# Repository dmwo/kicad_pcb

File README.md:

# kicad_pcb
 A collection of personal KiCAD PCBs

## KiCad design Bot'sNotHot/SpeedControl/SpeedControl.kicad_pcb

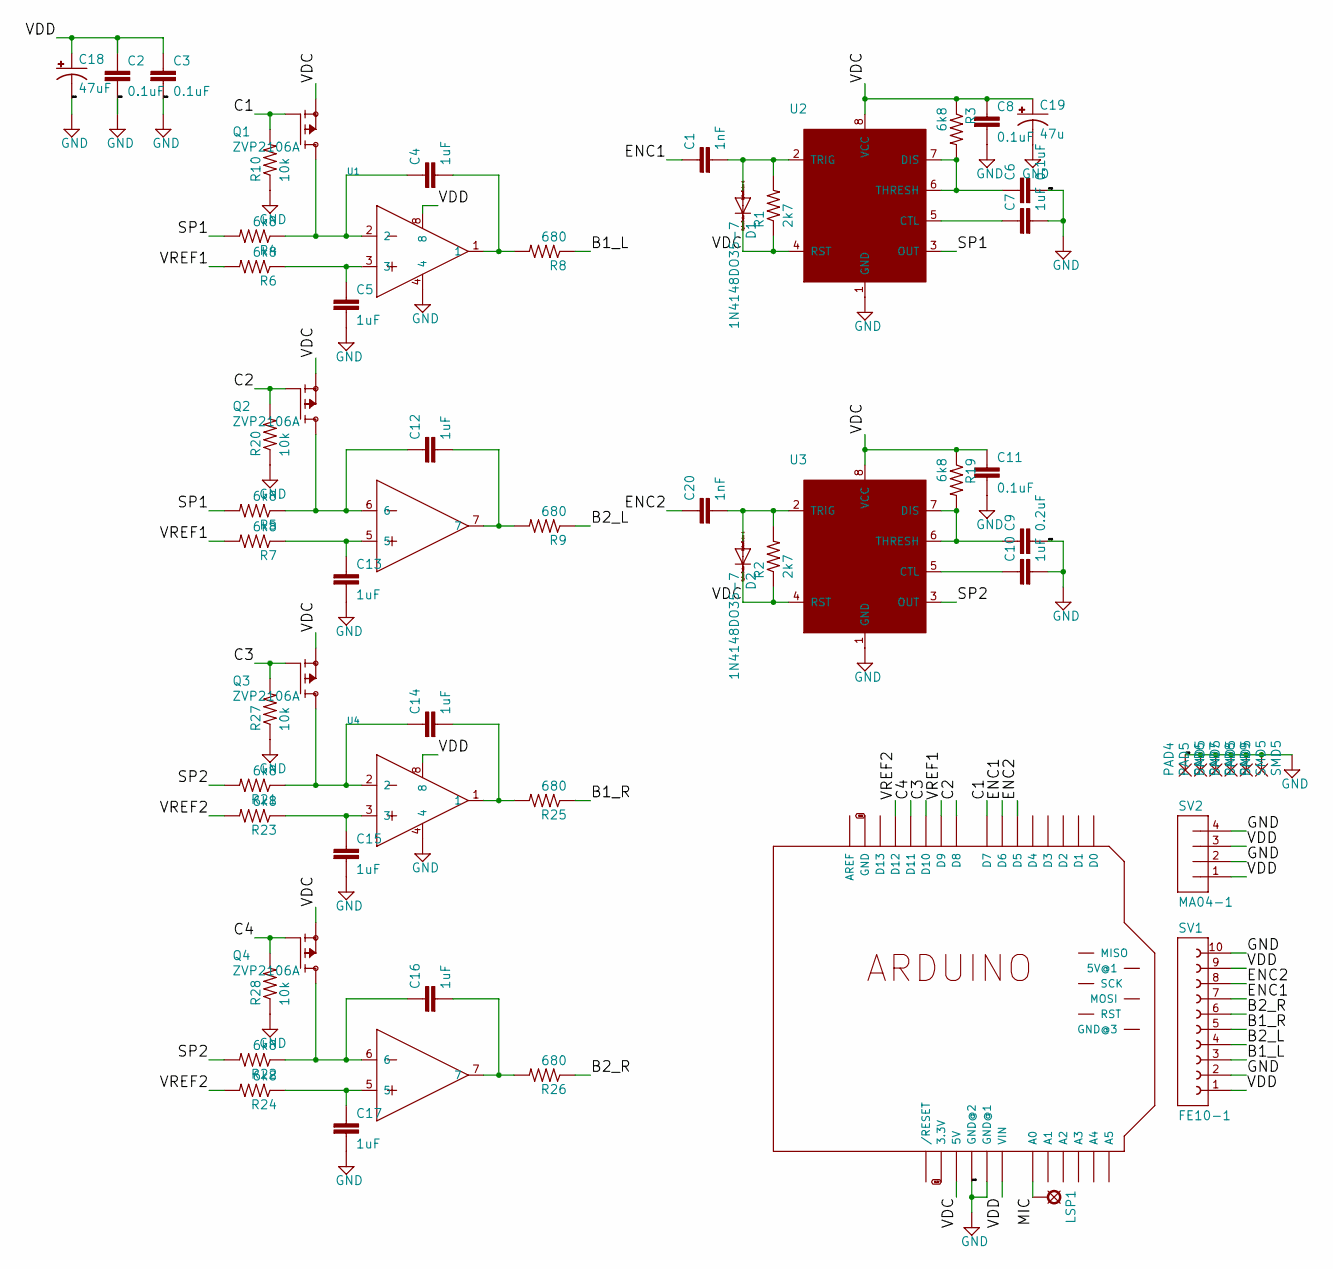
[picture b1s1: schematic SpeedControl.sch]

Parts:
C1, C20: 1nF; C0805
C2, C3, C6, C8, C11: 0.1uF; C0805
C4, C5, C7, C10, C12, C13, C14, C15, C16, C17: 1uF; C0805
C9: 0.2uF; C0805
C18: 47uF; PANASONIC_C
C19: 47u; PANASONIC_C
D1, D2: 1N4148DO35-7; DO35-7
LSP1: SE11
M1: ARDUINO_R3_ICSP_NODIM; ARDUINOR3_ICSP_NODIM
PAD4, PAD5, PAD6, PAD7, PAD8, PAD9: SMD5; SMD2,54-5,08
Q1, Q2, Q3, Q4: ZVP2106A; TO92-BCE
R1, R2: 2k7; R0805
R3, R4, R5, R6, R7, R19, R21, R22, R23, R24: 6k8; R0805
R8, R9, R25, R26: 680; R0805
R10, R20, R27, R28: 10k; R0805
SV1: FE10-1; FE10
SV2: MA04-1
U1, U4: TLV272; DIL08
U2, U3: 555CN; DIL08

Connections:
3.3V: M1.3V (3.3V)
/B1_L: R8.1, SV1.3
/B1_R: R25.1, SV1.5
/B2_L: R9.1, SV1.4
/B2_R: R26.1, SV1.6
/C1: M1.D7, Q1.G, R10.2
/C2: M1.D8, Q2.G, R20.2
/C3: M1.D10, Q3.G, R27.2
/C4: M1.D11, Q4.G, R28.2
/ENC1: C1.1, M1.D6, SV1.7
/ENC2: C20.1, M1.D5, SV1.8
/MIC: LSP1.MP, M1.A0
/SP1: R4.2, R5.2, U2.3 (OUT)
/SP2: R21.2, R22.2, U3.3 (OUT)
/VDC: C8.1, C11.1, C19.+, D1.C, D2.C, M1.5V, Q1.S, Q2.S, Q3.S, Q4.S, R1.1, R2.1, R3.1, R19.1, U2.4 (RST), U2.8 (VCC), U3.4 (RST), U3.8 (VCC)
/VDD: C2.1, C3.1, C18.+, M1.VIN, SV1.1, SV1.9, SV2.1, SV2.3, U1.8, U4.8
/VREF1: M1.D9, R6.2, R7.2
/VREF2: M1.D12, R23.2, R24.2
GND: C2.2, C3.2, C5.2, C6.2, C7.2, C8.2, C9.2, C10.2, C11.2, C13.2, C15.2, C17.2, C18.-, C19.-, M1.GND, M1.GND@1, M1.GND@2, PAD4.1, PAD5.1, PAD6.1, PAD7.1, PAD8.1, PAD9.1, R10.1, R20.1, R27.1, R28.1, SV1.2, SV1.10, SV2.2, SV2.4, U1.4, U2.1 (GND), U3.1 (GND), U4.4
unnamed: C1.2, D1.A, R1.2, U2.2 (TRIG)
unnamed: C4.1, Q1.D, R4.1, U1.2
unnamed: C4.2, R8.2, U1.1
unnamed: C5.1, R6.1, U1.3
unnamed: C6.1, R3.2, U2.6 (THRESH), U2.7 (DIS)
unnamed: C7.1, U2.5 (CTL)
unnamed: C9.1, R19.2, U3.6 (THRESH), U3.7 (DIS)
unnamed: C10.1, U3.5 (CTL)
unnamed: C12.1, Q2.D, R5.1, U1.6
unnamed: C12.2, R9.2, U1.7
unnamed: C13.1, R7.1, U1.5
unnamed: C14.1, Q3.D, R21.1, U4.2
unnamed: C14.2, R25.2, U4.1
unnamed: C15.1, R23.1, U4.3
unnamed: C16.1, Q4.D, R22.1, U4.6
unnamed: C16.2, R26.2, U4.7
unnamed: C17.1, R24.1, U4.5
unnamed: C20.2, D2.A, R2.2, U3.2 (TRIG)

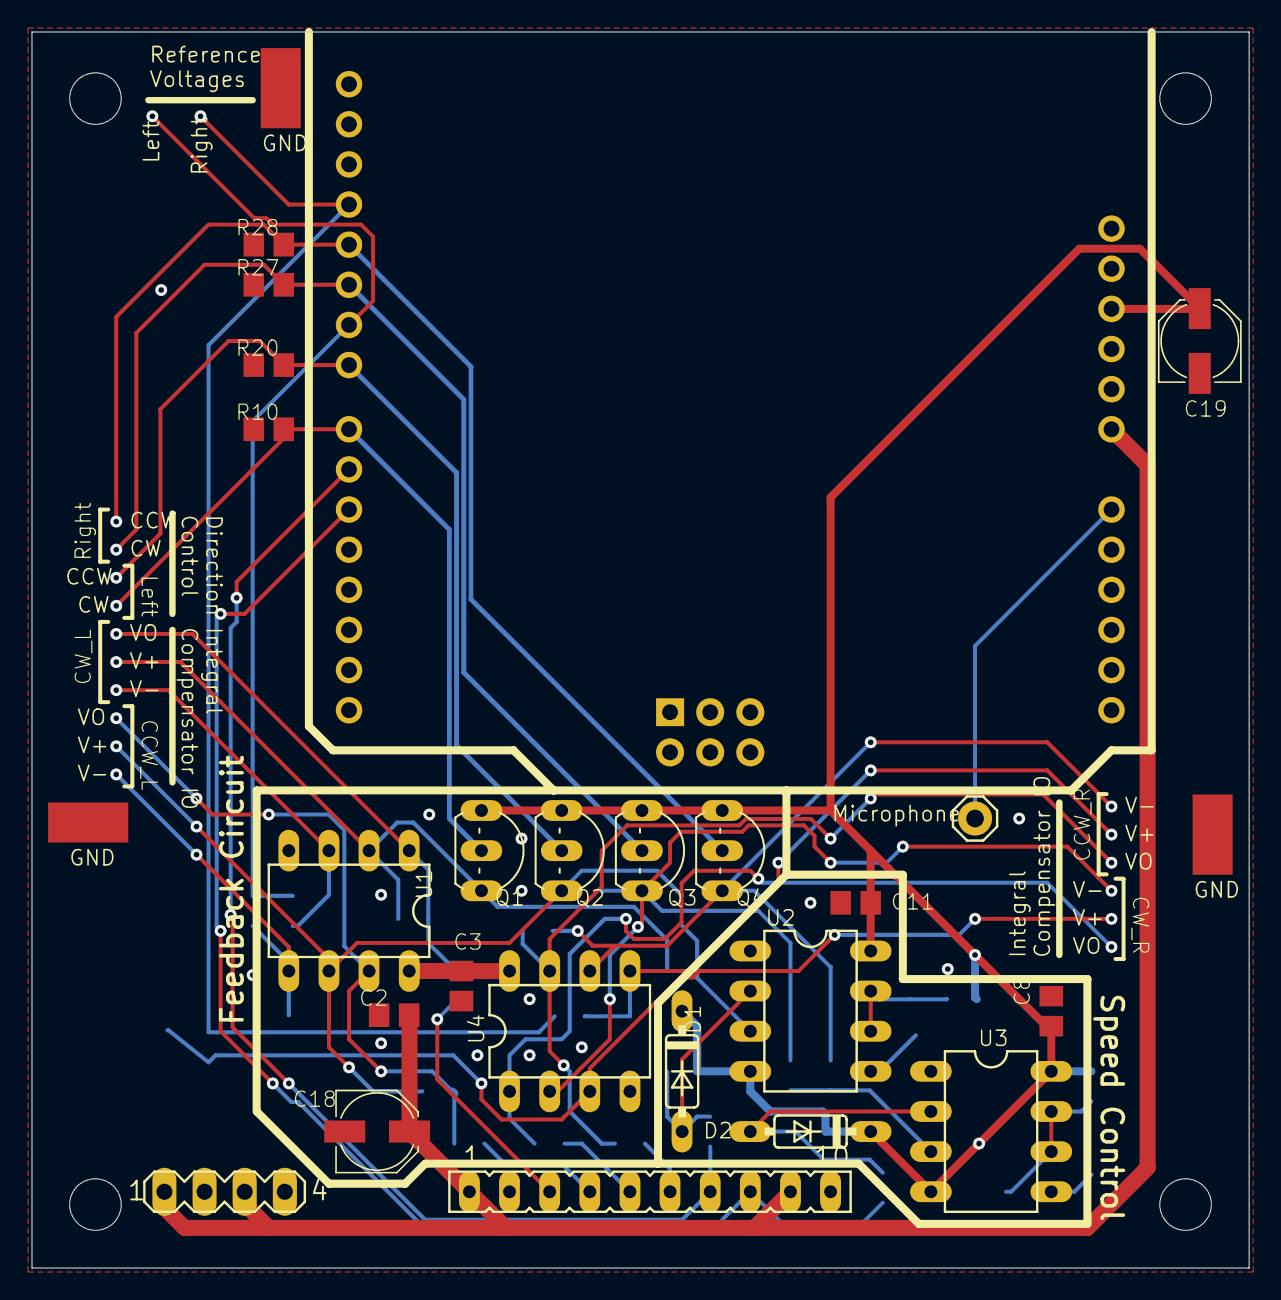
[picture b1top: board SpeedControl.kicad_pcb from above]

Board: 2 copper layers, 77.0 x 78.2 mm, 64 parts (0 on the bottom side), 36 nets.

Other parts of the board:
@HOLE0, @HOLE1, @HOLE2, @HOLE3: (no value)

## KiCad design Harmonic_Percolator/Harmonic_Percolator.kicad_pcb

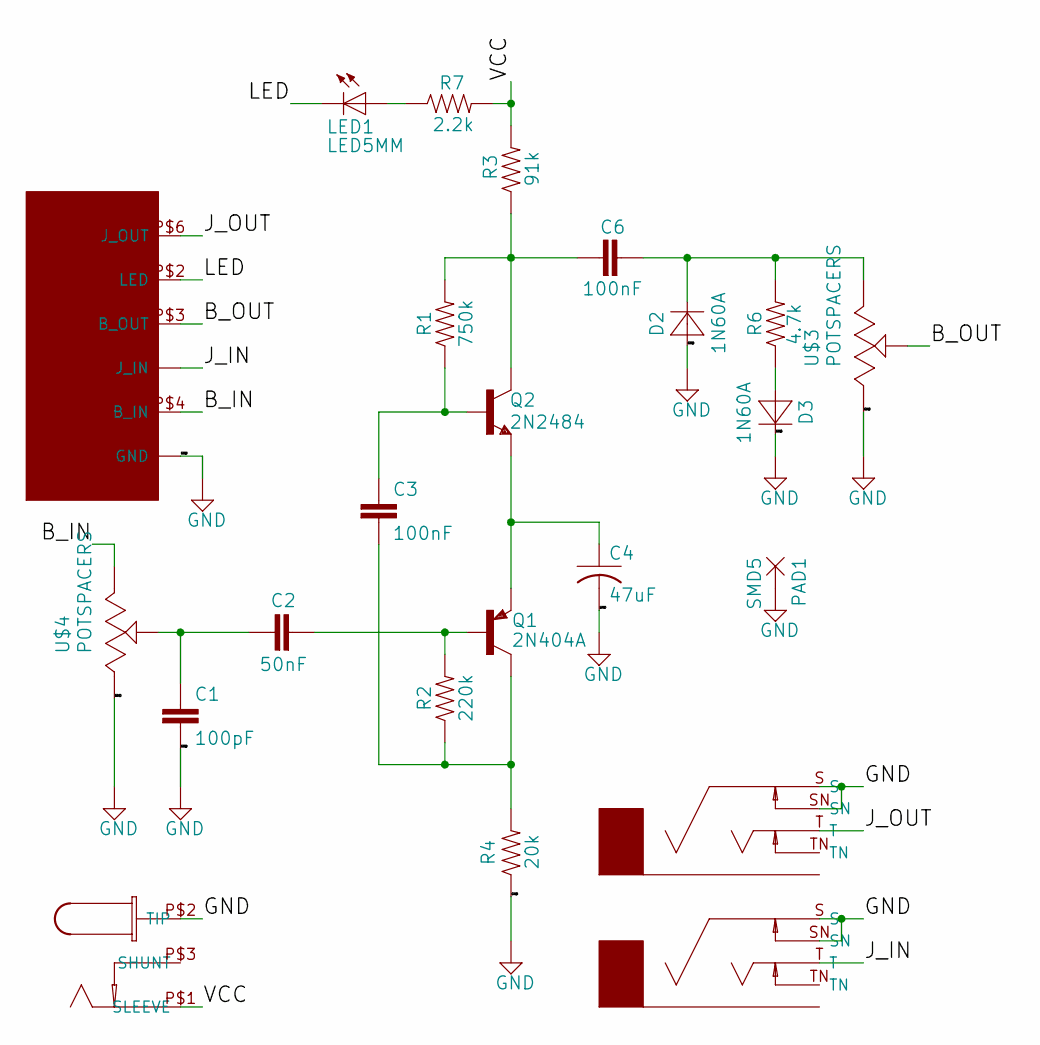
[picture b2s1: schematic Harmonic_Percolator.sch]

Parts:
C1: 100pF; C050-025X075
C2: 50nF; C150-054X183
C3, C6: 100nF; C050-024X044
C4: 47uF; C025-024X044
D2, D3: 1N60A; DO-7
LED1: LED5MM
PAD1: SMD5; SMD2,54-5,08
PS1: DCJACK
Q1: 2N404A; TO5
Q2: 2N2484; TO18
R1: 750k; 0207_7
R2: 220k; 0207_7
R3: 91k; 0207_7
R4: 20k; 0207_7
R6: 4.7k; 0207_7
R7: 2.2k; 0207_7
S1: FOOTSWITCH
U$1, U$2: NEUTRIKENCJACK
U$3, U$4: POTSPACERS

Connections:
/B_IN: S1.P$4 (B_IN), U$4.P$3 (E)
/B_OUT: S1.P$3 (B_OUT), U$3.P$2 (S)
/J_IN: S1.P$1 (J_IN), S1.P$9 (J_IN), U$2.T
/J_OUT: S1.P$6 (J_OUT), U$1.T
/LED: LED1.K (C), S1.P$2 (LED)
/VCC: PS1.P$1 (SLEEVE), R3.2, R7.2
GND: C1.2, C4.2, D2.P$2 (A), D3.P$1 (C), PAD1.1, PS1.P$2 (TIP), R4.1, S1.P$5 (GND), S1.P$7 (GND), U$1.S, U$1.SN, U$2.S, U$2.SN, U$3.P$1 (A), U$4.P$1 (A)
unnamed: C1.1, C2.1, U$4.P$2 (S)
unnamed: C2.2, Q1.2 (B), R2.2
unnamed: C3.1, Q2.2 (B), R1.1
unnamed: C3.2, Q1.3 (C), R2.1, R4.2
unnamed: C4.1, Q1.1 (E), Q2.1 (E)
unnamed: C6.1, Q2.3 (C), R1.2, R3.1
unnamed: C6.2, D2.P$1 (C), R6.2, U$3.P$3 (E)
unnamed: D3.P$2 (A), R6.1
unnamed: LED1.A, R7.1

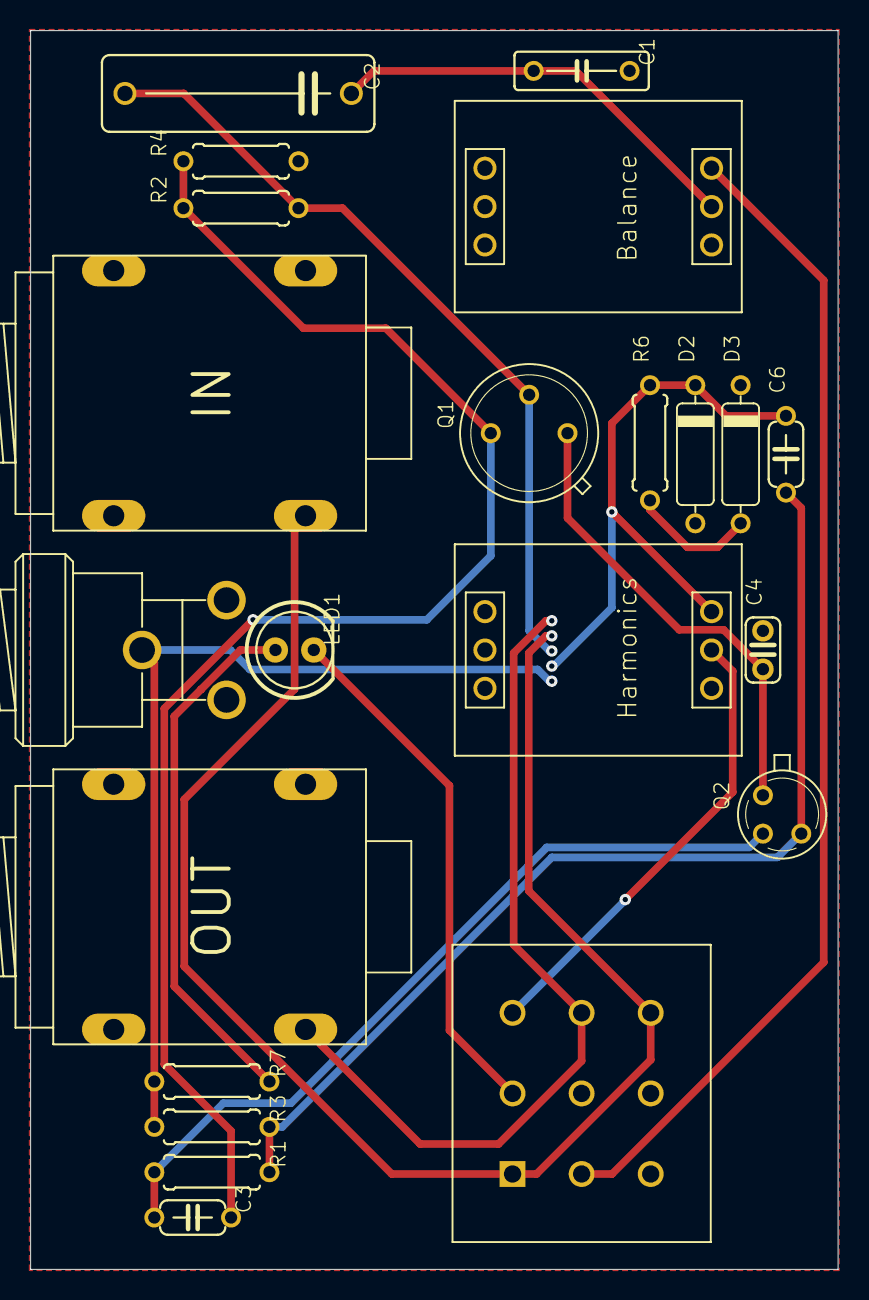
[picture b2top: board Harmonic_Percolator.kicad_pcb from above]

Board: 2 copper layers, 53.5 x 82.0 mm, 23 parts (0 on the bottom side), 16 nets.

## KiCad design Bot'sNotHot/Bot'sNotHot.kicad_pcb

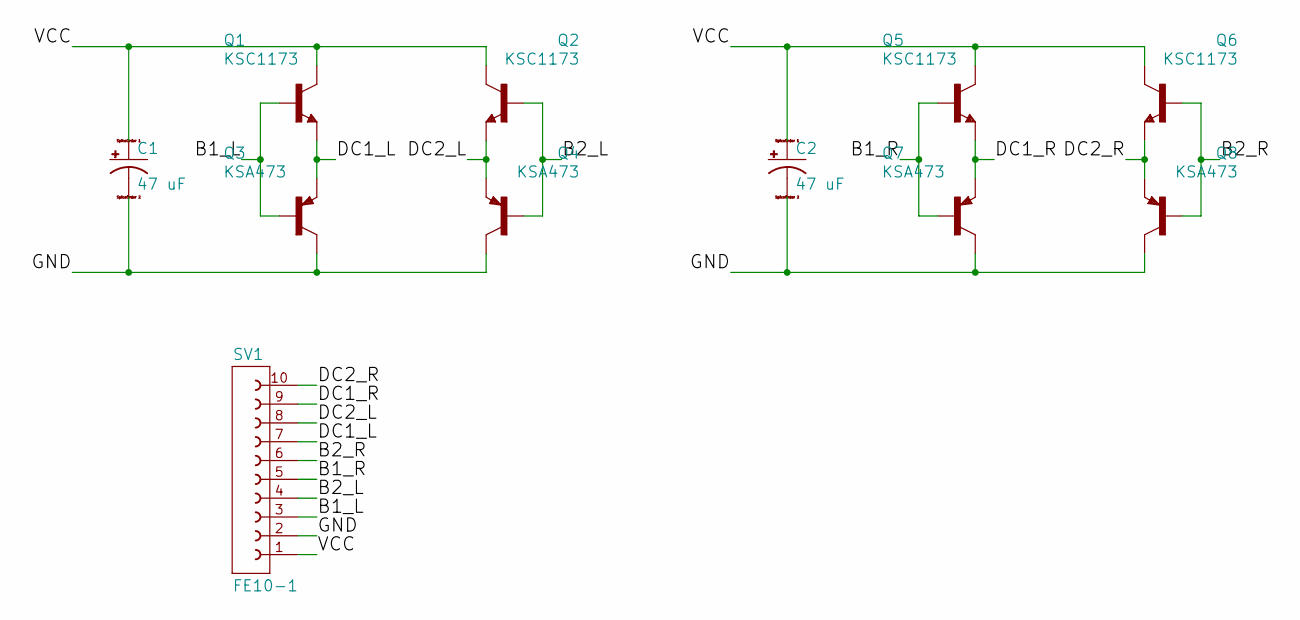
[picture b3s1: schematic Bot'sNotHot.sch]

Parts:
C1, C2: 47 uF; 140CLH-1010
Q1, Q2, Q5, Q6: KSC1173; MOSFET_HEATSINK
Q3, Q4, Q7, Q8: KSA473; MOSFET_HEATSINK
SV1: FE10-1; FE10

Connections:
/B1_L: Q1.1 (B), Q3.1 (B), SV1.3
/B1_R: Q5.1 (B), Q7.1 (B), SV1.5
/B2_L: Q2.1 (B), Q4.1 (B), SV1.4
/B2_R: Q6.1 (B), Q8.1 (B), SV1.6
/DC1_L: Q1.3 (E), Q3.3 (E), SV1.7
/DC1_R: Q5.3 (E), Q7.3 (E), SV1.9
/DC2_L: Q2.3 (E), Q4.3 (E), SV1.8
/DC2_R: Q6.3 (E), Q8.3 (E), SV1.10
/GND: C1.-, C2.-, Q3.2 (C), Q4.2 (C), Q7.2 (C), Q8.2 (C), SV1.2
/VCC: C1.+, C2.+, Q1.2 (C), Q2.2 (C), Q5.2 (C), Q6.2 (C), SV1.1

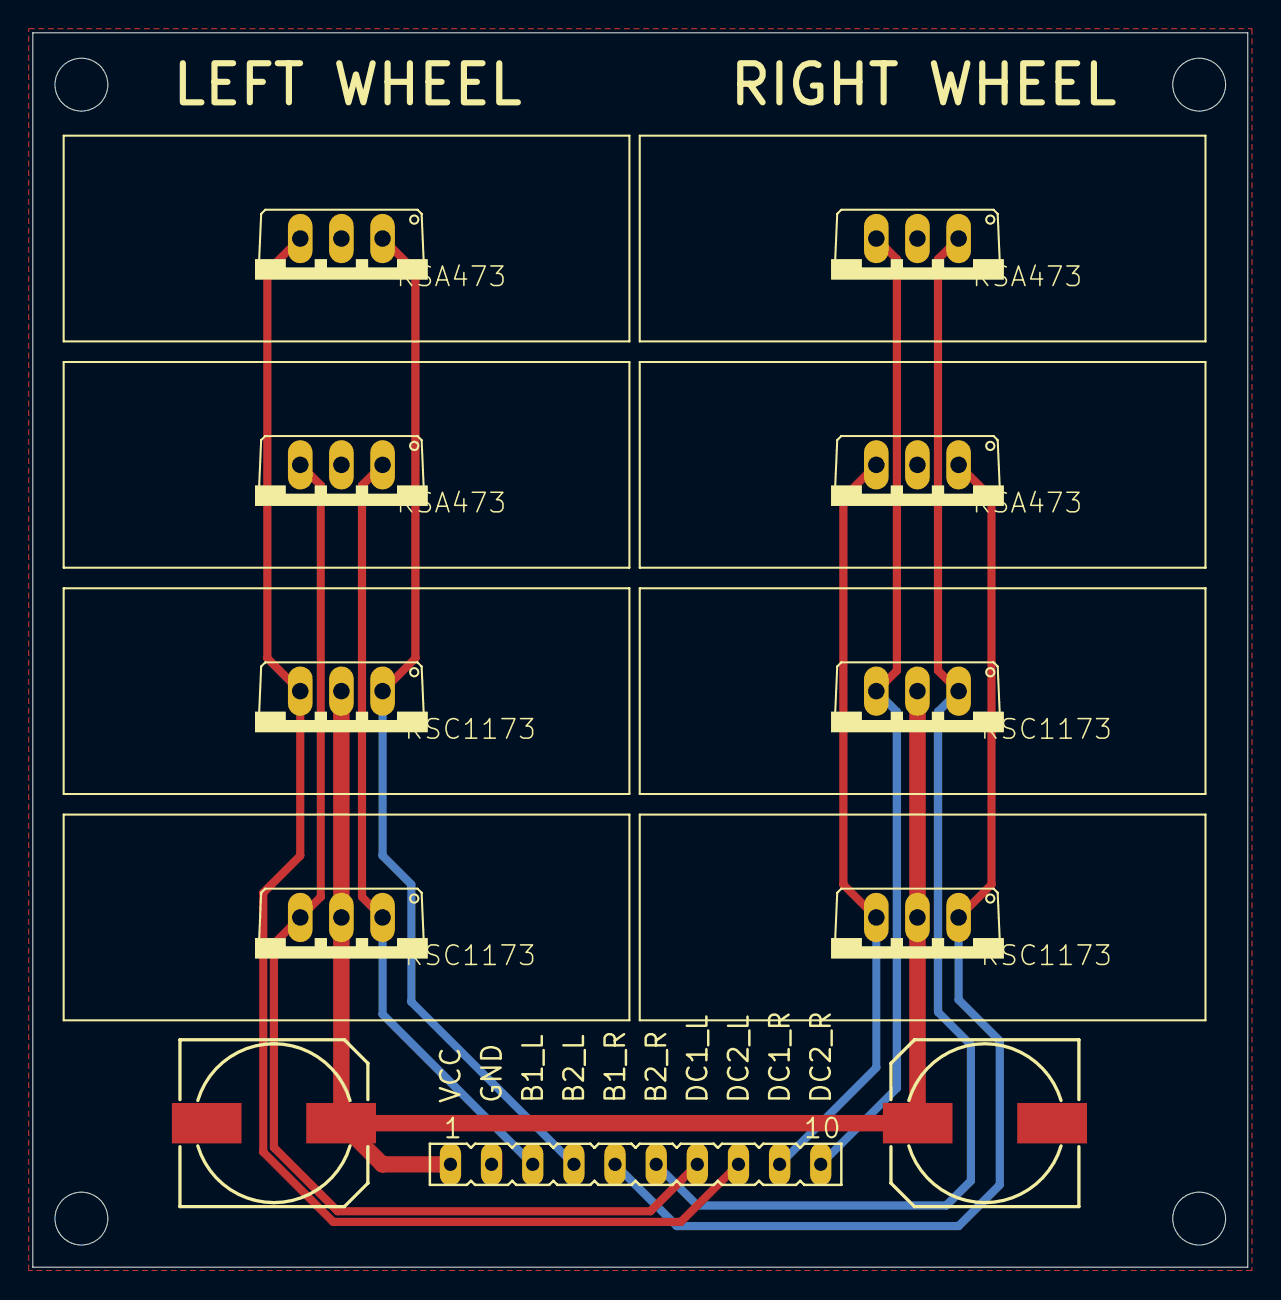
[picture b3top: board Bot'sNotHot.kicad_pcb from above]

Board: 2 copper layers, 75.0 x 76.2 mm, 15 parts (0 on the bottom side), 10 nets.

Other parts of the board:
@HOLE0, @HOLE1, @HOLE2, @HOLE3: (no value)

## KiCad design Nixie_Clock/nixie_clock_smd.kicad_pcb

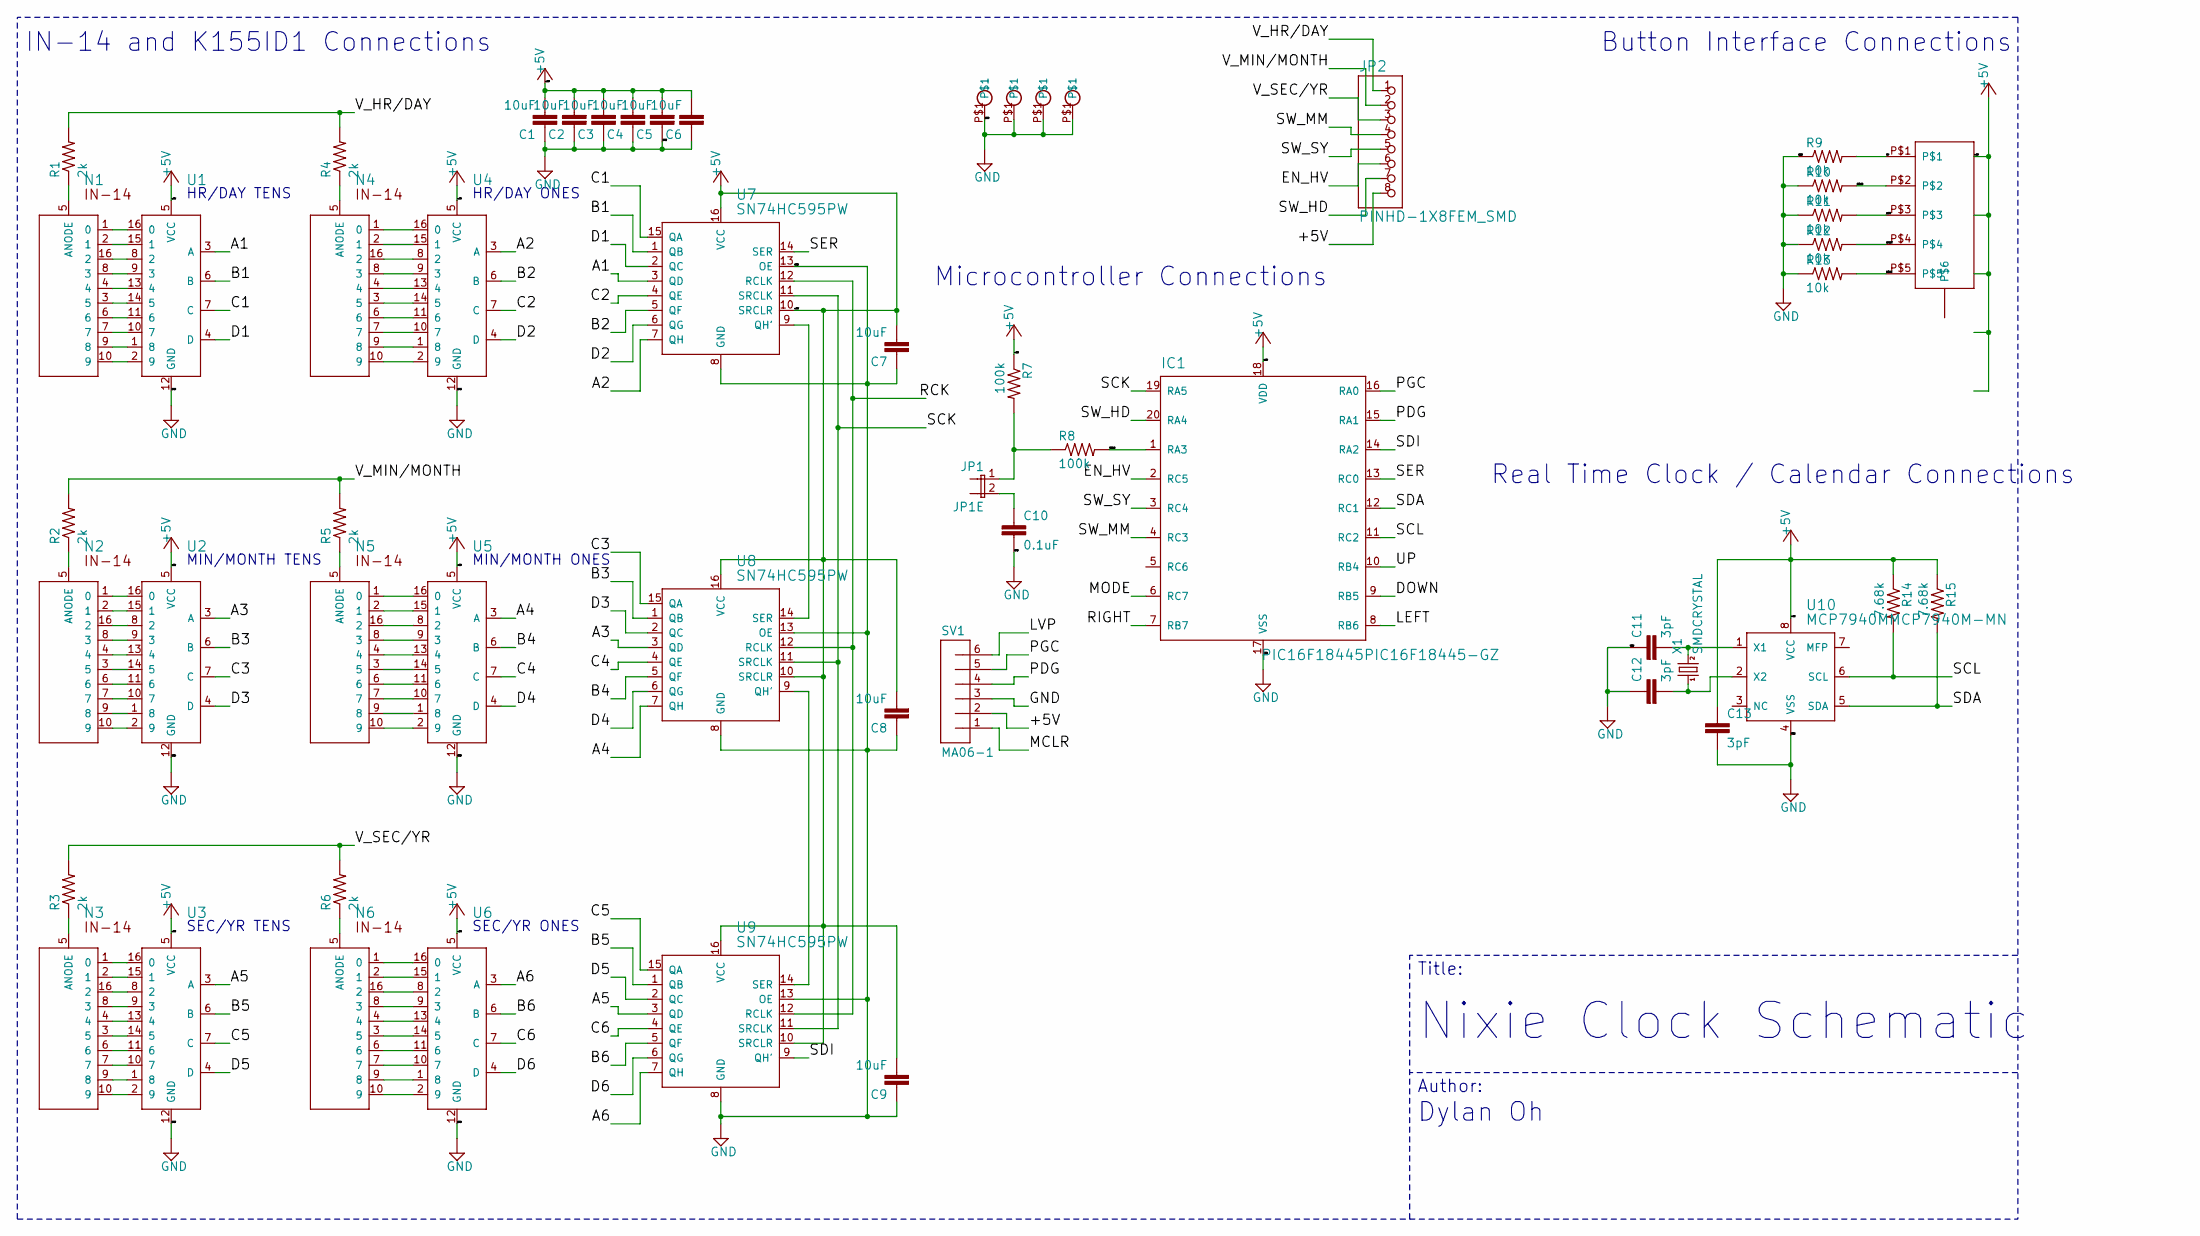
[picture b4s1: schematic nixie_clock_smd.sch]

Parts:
C1, C2, C3, C4, C5, C6, C7, C8, C9: 10uF; C0603
C10: 0.1uF; C0805
C11, C12, C13: 3pF; C0805
IC1: PIC16F18445PIC16F18445-GZ; UQFN-20
J1, J2, J3, J4: M3_HOLE; MOUNTING_HOLE
J5: PXC_1771059; TERMBLOCK_5
JP1: JP1E; JP1
JP2: PINHD-1X8FEM_SMD; SSM-108-XXX-SV
N1, N2, N3, N4, N5, N6: NIXIE_MOUNT
R1, R2, R3, R4, R5, R6: 2k; R0805
R7, R8: 100k; R0805
R9, R10, R11, R12, R13: 10k; R0805
R14, R15: 7.68k; R0805
SV1: MA06-1
U1, U2, U3, U4, U5, U6: K155ID1K155ID1_SMD; ICF-316-S-I
U7, U8, U9: SN74HC595PW; TSSOP16
U10: MCP7940MMCP7940M-MN; SON50P300X200X75-8
X1: SMDCRYSTAL

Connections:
+5V: C1.2, C2.2, C3.2, C4.2, C5.2, C6.2, C7.2, C8.2, C9.2, C13.1, IC1.18 (VDD), JP2.8, R7.1, R14.1, R15.1, SV1.2, U1.5 (VCC), U2.5 (VCC), U3.5 (VCC), U4.5 (VCC), U5.5 (VCC), U6.5 (VCC), U7.10 (SRCLR), U7.16 (VCC), U8.10 (SRCLR), U8.16 (VCC), U9.10 (SRCLR), U9.16 (VCC), U10.8 (VCC)
/A1: U1.3 (A), U7.3 (QD)
/A2: U4.3 (A), U7.7 (QH)
/A3: U2.3 (A), U8.3 (QD)
/A4: U5.3 (A), U8.7 (QH)
/A5: U3.3 (A), U9.3 (QD)
/A6: U6.3 (A), U9.7 (QH)
/B1: U1.6 (B), U7.1 (QB)
/B2: U4.6 (B), U7.5 (QF)
/B3: U2.6 (B), U8.1 (QB)
/B4: U5.6 (B), U8.5 (QF)
/B5: U3.6 (B), U9.1 (QB)
/B6: U6.6 (B), U9.5 (QF)
/C1: U1.7 (C), U7.15 (QA)
/C2: U4.7 (C), U7.4 (QE)
/C3: U2.7 (C), U8.15 (QA)
/C4: U5.7 (C), U8.4 (QE)
/C5: U3.7 (C), U9.15 (QA)
/C6: U6.7 (C), U9.4 (QE)
/D1: U1.4 (D), U7.2 (QC)
/D2: U4.4 (D), U7.6 (QG)
/D3: U2.4 (D), U8.2 (QC)
/D4: U5.4 (D), U8.6 (QG)
/D5: U3.4 (D), U9.2 (QC)
/D6: U6.4 (D), U9.6 (QG)
/DOWN: IC1.9 (RB5), J5.P$2, R10.2
/EN_HV: IC1.2 (RC5), JP2.6
/LEFT: IC1.8 (RB6), J5.P$3, R11.2
/LVP: SV1.6
/MCLR: IC1.1 (RA3), R8.2, SV1.1
/MODE: IC1.6 (RC7), J5.P$5, R13.2
/PDG: IC1.15 (RA1), SV1.4
/PGC: IC1.16 (RA0), SV1.5
/RCK: U7.12 (RCLK), U8.12 (RCLK), U9.12 (RCLK)
/RIGHT: IC1.7 (RB7), J5.P$4, R12.2
/SCK: IC1.19 (RA5), U7.11 (SRCLK), U8.11 (SRCLK), U9.11 (SRCLK)
/SCL: IC1.11 (RC2), R14.2, U10.6 (SCL)
/SDA: IC1.12 (RC1), R15.2, U10.5 (SDA)
/SDI: IC1.14 (RA2), U9.9 (QH')
/SER: IC1.13 (RC0), U7.14 (SER)
/SW_HD: IC1.20 (RA4), JP2.7
/SW_MM: IC1.4 (RC3), JP2.4
/SW_SY: IC1.3 (RC4), JP2.5
/UP: IC1.10 (RB4), J5.P$1, R9.2
/V_HR/DAY: JP2.1, R1.2, R4.2
/V_MIN/MONTH: JP2.2, R2.2, R5.2
/V_SEC/YR: JP2.3, R3.2, R6.2
GND: C1.1, C2.1, C3.1, C4.1, C5.1, C6.1, C7.1, C8.1, C9.1, C10.2, C11.1, C12.1, C13.2, IC1.17 (VSS), J1.P$1, J2.P$1, J3.P$1, J4.P$1, R9.1, R10.1, R11.1, R12.1, R13.1, SV1.3, U1.12 (GND), U2.12 (GND), U3.12 (GND), U4.12 (GND), U5.12 (GND), U6.12 (GND), U7.8 (GND), U7.13 (OE), U8.8 (GND), U8.13 (OE), U9.8 (GND), U9.13 (OE), U10.4 (VSS)
unnamed: C10.1, JP1.2
unnamed: C11.2, U10.1 (X1), X1.P$2 (2)
unnamed: C12.2, U10.2 (X2), X1.P$1 (1)
unnamed: J5.P$6, J5.P$7
unnamed: JP1.1, R7.2, R8.1
unnamed: N1.1 (0), U1.16 (0)
unnamed: N1.2 (1), U1.15 (1)
unnamed: N1.3 (5), U1.14 (5)
unnamed: N1.4, U1.13 (4)
unnamed: N1.5 (ANODE), R1.1
unnamed: N1.6, U1.11 (6)
unnamed: N1.7, U1.10 (7)
unnamed: N1.8 (3), U1.9 (3)
unnamed: N1.9 (8), U1.1 (8)
unnamed: N1.10 (9), U1.2 (9)
unnamed: N1.16 (2), U1.8 (2)
unnamed: N2.1 (0), U2.16 (0)
unnamed: N2.2 (1), U2.15 (1)
unnamed: N2.3 (5), U2.14 (5)
unnamed: N2.4, U2.13 (4)
unnamed: N2.5 (ANODE), R2.1
unnamed: N2.6, U2.11 (6)
unnamed: N2.7, U2.10 (7)
unnamed: N2.8 (3), U2.9 (3)
unnamed: N2.9 (8), U2.1 (8)
unnamed: N2.10 (9), U2.2 (9)
unnamed: N2.16 (2), U2.8 (2)
unnamed: N3.1 (0), U3.16 (0)
unnamed: N3.2 (1), U3.15 (1)
unnamed: N3.3 (5), U3.14 (5)
unnamed: N3.4, U3.13 (4)
unnamed: N3.5 (ANODE), R3.1
unnamed: N3.6, U3.11 (6)
unnamed: N3.7, U3.10 (7)
unnamed: N3.8 (3), U3.9 (3)
unnamed: N3.9 (8), U3.1 (8)
unnamed: N3.10 (9), U3.2 (9)
unnamed: N3.16 (2), U3.8 (2)
unnamed: N4.1 (0), U4.16 (0)
unnamed: N4.2 (1), U4.15 (1)
unnamed: N4.3 (5), U4.14 (5)
unnamed: N4.4, U4.13 (4)
unnamed: N4.5 (ANODE), R4.1
unnamed: N4.6, U4.11 (6)
unnamed: N4.7, U4.10 (7)
unnamed: N4.8 (3), U4.9 (3)
unnamed: N4.9 (8), U4.1 (8)
unnamed: N4.10 (9), U4.2 (9)
unnamed: N4.16 (2), U4.8 (2)
unnamed: N5.1 (0), U5.16 (0)
unnamed: N5.2 (1), U5.15 (1)
unnamed: N5.3 (5), U5.14 (5)
unnamed: N5.4, U5.13 (4)
unnamed: N5.5 (ANODE), R5.1
unnamed: N5.6, U5.11 (6)
unnamed: N5.7, U5.10 (7)
unnamed: N5.8 (3), U5.9 (3)
unnamed: N5.9 (8), U5.1 (8)
unnamed: N5.10 (9), U5.2 (9)
unnamed: N5.16 (2), U5.8 (2)
unnamed: N6.1 (0), U6.16 (0)
unnamed: N6.2 (1), U6.15 (1)
unnamed: N6.3 (5), U6.14 (5)
unnamed: N6.4, U6.13 (4)
unnamed: N6.5 (ANODE), R6.1
unnamed: N6.6, U6.11 (6)
unnamed: N6.7, U6.10 (7)
unnamed: N6.8 (3), U6.9 (3)
unnamed: N6.9 (8), U6.1 (8)
unnamed: N6.10 (9), U6.2 (9)
unnamed: N6.16 (2), U6.8 (2)
unnamed: U7.9 (QH'), U8.14 (SER)
unnamed: U8.9 (QH'), U9.14 (SER)

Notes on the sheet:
HR/DAY TENS
HR/DAY ONES
MIN/MONTH TENS
MIN/MONTH ONES
SEC/YR TENS
SEC/YR ONES
IN-14 and K155ID1 Connections
Button Interface Connections
Nixie Clock Schematic
Dylan Oh
Title:
Author:
Microcontroller Connections
Real Time Clock / Calendar Connections

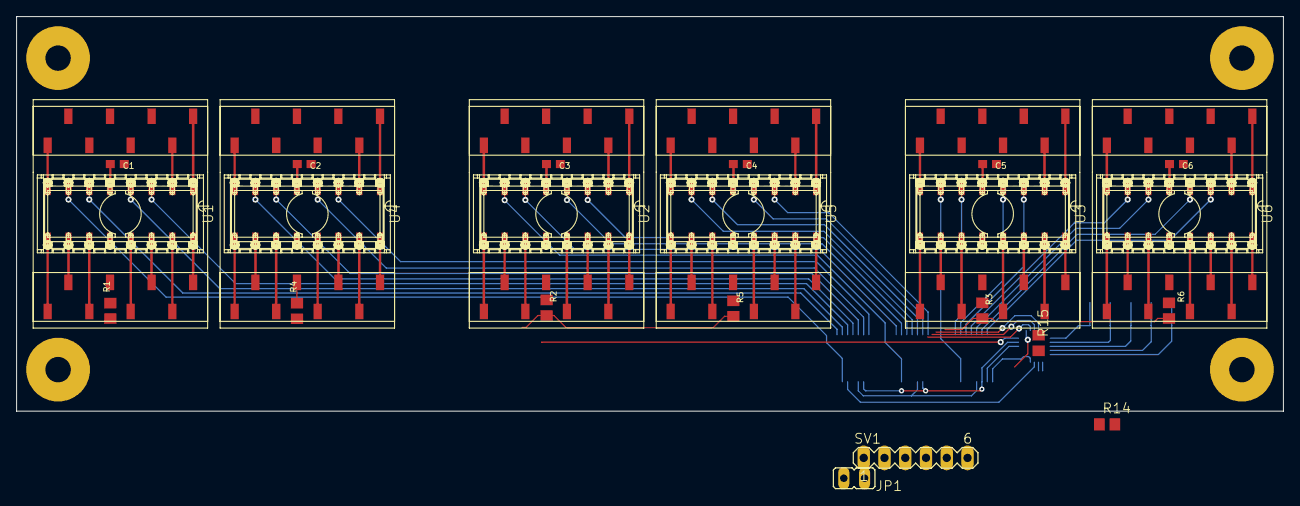
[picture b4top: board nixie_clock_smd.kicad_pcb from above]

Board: 2 copper layers, 154.9 x 48.3 mm, 54 parts (0 on the bottom side), 120 nets.

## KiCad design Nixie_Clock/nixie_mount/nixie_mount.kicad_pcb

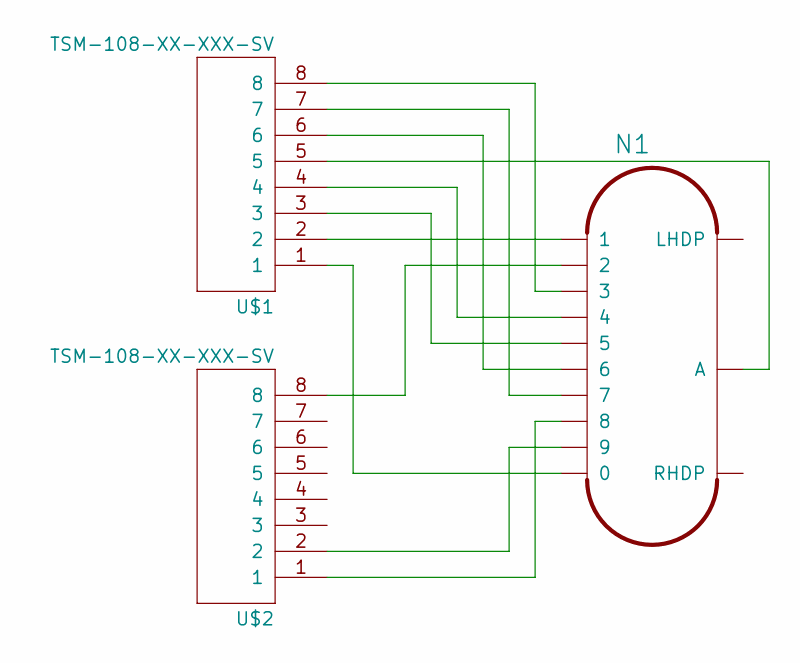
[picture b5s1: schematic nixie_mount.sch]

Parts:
N1: IN-14
U$1, U$2: TSM-108-XX-XXX-SV

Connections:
unnamed: N1.0, U$1.1
unnamed: N1.1, U$1.2
unnamed: N1.2, U$2.8
unnamed: N1.3, U$1.8
unnamed: N1.4, U$1.4
unnamed: N1.5, U$1.3
unnamed: N1.6, U$1.6
unnamed: N1.7, U$1.7
unnamed: N1.8, U$2.1
unnamed: N1.9, U$2.2
unnamed: N1.A, U$1.5

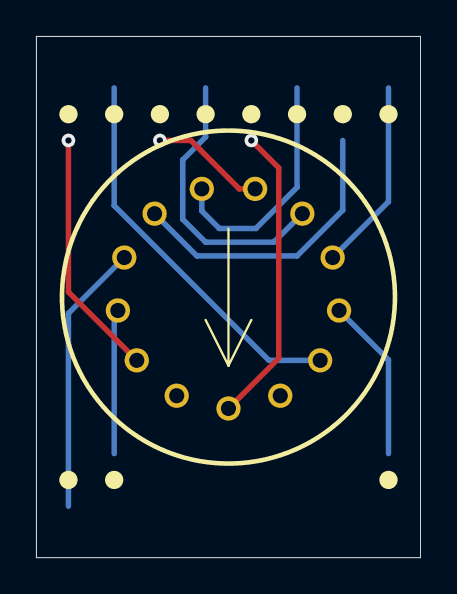
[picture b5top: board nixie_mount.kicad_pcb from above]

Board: 2 copper layers, 21.3 x 29.0 mm, 3 parts (0 on the bottom side), 11 nets.
